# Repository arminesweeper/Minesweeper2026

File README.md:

# Assiut Robotics — Minesweeper Autonomous Rover

<p align="center">

</p>

---

## 📌 Executive Summary

The **Assiut Robotics Minesweeper Rover** is an autonomous field robotics platform engineered for humanitarian mine action and robotics competitions (*Minesweeper International / Minesweeper Egypt*). The rover combines real-time computer vision, electromagnetic/inductive sensing, optical proximity scanning, autonomous coverage planning, closed-loop motion control, and surface mine extraction mechanics into an integrated cross-layer cyber-physical system.

- **Institution:** Faculty of Engineering, Assiut University
- **Team:** Assiut Robotics Team
- **Supervisor:** Eng. Sayed Khader
- **Demonstration Video:** [YouTube — Minesweeper Robot](https://youtu.be/dL5ubC7n4h4)

---

## 📖 Master Documentation Navigation Hub

This repository contains multi-tiered engineering documentation covering software, firmware, electronics, and competition field strategy. Use the quick links below to navigate to specific subsystems:

| Document | Description | Language | Primary Location |
| :--- | :--- | :---: | :--- |
| **Competition Overview & Technical Report** | Comprehensive engineering report, real-world bug troubleshooting, competition strategy, and mathematical models | Arabic | [`Minesweeper_Competitions_Overview.md`](./Minesweeper_Competitions_Overview.md) |
| **Electronic Circuit & Hardware Report** | Full PCB schematic analysis, power distribution rails, relay drivers, connectors, and BOM | English | [`Minesweeper2026/Files/Report/report.md`](./Minesweeper2026/Files/Report/report.md) |
| **ROS 2 Workspace Manual** | Simulation, SLAM Toolbox, Navigation, Zigzag Coverage, Vision OCR, and launch guides | English | [`rover_ws/README.md`](./rover_ws/README.md) |
| **Synchronized Pinout Map** | As-fabricated Mega 2560 pin mappings, timers, interrupts, and Soft-I2C flying leads | English | [`Minesweeper2026/Arduino/MotorController/Docs/Pinout.md`](./Minesweeper2026/Arduino/MotorController/Docs/Pinout.md) |
| **Firmware Architecture** | Object-oriented modular firmware breakdown, FSM state machines, and task loop timing | English | [`Minesweeper2026/Arduino/MotorController/Docs/Architecture.md`](./Minesweeper2026/Arduino/MotorController/Docs/Architecture.md) |
| **Serial Protocol & API** | Framing, command bytes, packet checksums, and telemetry stream formats | English | [`Minesweeper2026/Arduino/MotorController/Docs/Communication.md`](./Minesweeper2026/Arduino/MotorController/Docs/Communication.md) |
| **Motion Control & PID** | Kinematics, PID math, feed-forward, deadband thresholds, and odometry formulas | English | [`Minesweeper2026/Arduino/MotorController/Docs/MotionControl.md`](./Minesweeper2026/Arduino/MotorController/Docs/MotionControl.md) |
| **Safety & Watchdog Systems** | Communication timeouts, brownout protection, limit switch safety, and E-Stop states | English | [`Minesweeper2026/Arduino/MotorController/Docs/Safety.md`](./Minesweeper2026/Arduino/MotorController/Docs/Safety.md) |
| **Wiring & Harness Manual** | Wire gauges, connector specifications, terminal assignments, and crimping guide | English | [`Minesweeper2026/Arduino/MotorController/Docs/WiringManual.md`](./Minesweeper2026/Arduino/MotorController/Docs/WiringManual.md) |
| **Operator GUI & Telemetry** | PySide6 desktop dashboard, gamepad integration, and live telemetry viewer | English | [`Minesweeper2026/GUI/README.md`](./Minesweeper2026/GUI/README.md) |
| **Legacy 2024 Archive** | Historic codebase, design iterations, and legacy project records | English | [`Minesweeper2024/README.md`](./Minesweeper2024/README.md) |

---

## 🏛️ System Architecture

The robot utilizes a **hierarchical dual-interface architecture** providing robust separation of concerns between high-level computation, real-time deterministic control, and standalone field debugging:

```mermaid
flowchart TB
    subgraph OperatorLayer["Operator & Telemetry Station"]
        OP_STATION[Operator Laptop / Gamepad]
        WEB_CLIENT[Browser Diagnostic UI / WebSockets]
    end

    subgraph HighLevelCompute["High-Level Compute — Raspberry Pi 4 (Ubuntu Linux)"]
        ROS_CORE[ROS 2 Humble Middleware]
        SLAM_NODE[SLAM Toolbox / EKF Localization]
        PLAN_NODE[Zigzag Coverage & A* Planner]
        VISION_NODE[Camera + EasyOCR Mine Classifier]
        SER_NODE[Serial Bridge Interface Node]
    end

    subgraph WirelessBypass["Field Diagnostics Bypass — ESP8266 Module"]
        ESP_CORE[ESP8266 Local Web Server]
        ESP_JOY[WASD / Touchscreen Teleop]
        ESP_TELEM[Live Battery & Sensor Telemetry]
    end

    subgraph LowLevelControl["Deterministic Embedded Controller — Arduino Mega 2560"]
        STATE_MGR[System State Machine INIT / ARMED / RUN / FAULT]
        PID_CORE[Dual Wheel PID Controller + Feed-Forward]
        MOTION_CORE[Differential Drive Inverse Kinematics]
        ODOM_CORE[Encoder Odometry Accumulator]
        SAFETY_CORE[Watchdog, Brownout & E-Stop Interlocks]
        LIFT_CORE[Surface Mine Lift & Limit Switch Sequencer]
    end

    subgraph PowerAndActuation["Power Stage & Motor Drivers"]
        BATTERY[Tianneng 12V 25Ah Graphene Battery]
        CYTRON_DRV[Cytron MDD10A Rev2.0 Dual H-Bridge]
        DRIVE_MOTORS[4x High-Torque Geared DC Drive Motors]
        LIFT_MOTOR[Tailgate Extraction Lift Motor]
        RELAY_K1[Relay K1: Electromagnet Bus MAG1-MAG5]
        RELAY_K2[Relay K2: 12V Alert Siren & Strobe]
    end

    subgraph SensorArray["Detection & Navigation Sensors"]
        ENCODERS[Quadrature Optical Encoders PPR 385]
        IMU_6DOF[MPU6050 6-DOF IMU via Soft-I2C]
        PROX_ARRAY[5x Infrared Proximity Array + OR Gate]
        COIL_MD[Pulse Induction / VLF Metal Detector Coil]
        LIMIT_SW[Travel Limit Switches Active-LOW]
        VOLT_DIV[Precision 3.3:1 Battery Voltage Divider]
    end

    OP_STATION <-->|Wi-Fi 5 GHz / TCP Socket| ROS_CORE
    WEB_CLIENT <-->|Wi-Fi 2.4 GHz AP / HTTP| ESP_CORE
    
    ROS_CORE <-->|USB Serial0 / 115200 baud| LowLevelControl
    ESP_CORE <-->|Hardware Serial2 / 115200 baud| LowLevelControl

    LowLevelControl --> CYTRON_DRV --> DRIVE_MOTORS
    LowLevelControl --> LIFT_MOTOR
    LowLevelControl --> RELAY_K1
    LowLevelControl --> RELAY_K2

    ENCODERS --> LowLevelControl
    IMU_6DOF --> LowLevelControl
    PROX_ARRAY --> LowLevelControl
    COIL_MD --> LowLevelControl
    LIMIT_SW --> LowLevelControl
    VOLT_DIV --> LowLevelControl
    BATTERY --> PowerAndActuation
```

---

## ⚙️ Technical Specifications

### Physical & Mechanical

- **Locomotion:** 4-Wheel Drive (4WD) with differential skid-steering
- **Chassis Dimensions:** Length 650 mm × Width 480 mm × Ground Clearance 85 mm
- **Wheel Specifications:** 220 mm diameter × 100 mm width rugged rubber tread
- **Track Gauge (Wheelbase):** $L = 150\text{ mm}$ (center-to-center lateral base)
- **Mine Extraction:** Motorized tailgate lift with active limit switch homing and 5× high-flux electromagnets

### Electrical & Power Distribution

- **Main Power Source:** Tianneng TNE12-25 12V 25Ah Deep-Cycle Graphene Lead-Acid Battery
- **Motor Driver:** Cytron MDD10A Rev2.0 (Dual Channel, 10A continuous / 30A peak per channel)
- **Power Rails:**
  - `12V_MAIN`: Motors, Cytron H-Bridge, and auxiliary power (Terminal `J24`, filtered with $2000\,\mu\text{F}$)
  - `12V_MG`: Dedicated electromagnet bus (Terminals `MAG1–MAG5`, filtered with $4000\,\mu\text{F}$)
  - `5V_LOGIC`: MCU logic, encoders, IMU, sensors (Terminal `J22`, filtered with $2000\,\mu\text{F}$)
  - `5V_SERVO`: Camera pan servo and auxiliary servos (Terminal `J23`/`J13`)
- **Total Bulk Decoupling Capacitance:** $> 11,000\,\mu\text{F}$ distributed to suppress inductive motor inrush

### Microcontroller & Sensors

- **Low-Level MCU:** Atmel ATmega2560 (16 MHz, 8 KB SRAM, 256 KB Flash)
- **Encoder Resolution:** 385 pulses per revolution (PPR) on output wheel shaft
- **Inertial Measurement Unit:** InvenSense MPU6050 (6-DOF Accelerometer + Gyroscope) via Soft-I2C on D31/D33
- **Surface Detection:** 5× Infrared optical proximity sensors (`APRX1–APRX5`) with hardware OR-gate aggregation
- **Subsurface Detection:** High-sensitivity inductive search coil (`J40`) for buried metallic mines

---

## 🚀 Quick Start Guide

### 1. Arduino Mega Firmware

1. Open [`Minesweeper2026/Arduino/MotorController/MotorController.ino`](./Minesweeper2026/Arduino/MotorController/MotorController.ino) in the Arduino IDE or VS Code / PlatformIO.
2. Select Board: **Arduino Mega 2560**, Processor: **ATmega2560**.
3. Verify feature flags in `Config.h`:

   ```cpp
   #define ENABLE_WATCHDOG        1
   #define ENABLE_ODOMETRY        1
   #define ENABLE_LIFT            1
   #define ENABLE_SENSORS         1
   #define USE_SOFT_I2C_FOR_IMU   1
   ```

4. Compile and flash to the Arduino Mega via USB.

### 2. Standalone ESP8266 Telemetry & Debugging Dashboard

1. Open [`Minesweeper2026/Arduino/WiFiController/`](./Minesweeper2026/Arduino/WiFiController/) in the Arduino IDE.
2. Connect an Arduino Uno with `RESET` tied to `GND` as a hardware bypass programmer (`TX` to `TX`, `RX` to `RX`).
3. Flash the code to the ESP8266.
4. Power the rover, connect your phone or laptop to the created Wi-Fi Access Point (`Minesweeper_Rover`), and browse to `http://192.168.4.1` for full manual control, battery monitoring, and telemetry.

### 3. ROS 2 Workspace (Ubuntu Linux with ROS 2 Humble)

Clone or navigate to the workspace, install system dependencies, and build:

```bash
cd rover_ws
rosdep update
rosdep install --from-paths src --ignore-src -r -y
colcon build --symlink-install
source install/setup.bash
```

#### Launching Gazebo Simulation

```bash
ros2 launch rover_bringup simulated_robot.launch.py
```

#### Launching on the Physical Robot

```bash
ros2 launch rover_bringup real_robot.launch.py
```

#### Running Joystick Teleoperation

```bash
ros2 launch rover_controller joystick_teleop.launch.py
```

---

## 📡 ROS 2 Topics & Interfaces

| Topic | Message Type | Description |
| :--- | :--- | :--- |
| `/cmd_vel` | `geometry_msgs/msg/Twist` | Target linear and angular velocity commands |
| `/odom` | `nav_msgs/msg/Odometry` | Wheel odometry fused with encoder ticks |
| `/imu/data` | `sensor_msgs/msg/Imu` | Filtered angular velocity and linear acceleration |
| `/joint_states` | `sensor_msgs/msg/JointState` | Rover wheel and lift joint positions |
| `/scan` | `sensor_msgs/msg/LaserScan` | 2D LiDAR range scan for obstacle avoidance |
| `/map` | `nav_msgs/msg/OccupancyGrid` | Live SLAM occupancy grid map |
| `/coverage_path` | `nav_msgs/msg/Path` | Zigzag lawnmower path generated by planner |
| `/mine_detected` | `rover_msgs/msg/MineAlert` | Detected mine payload (type: surface/buried, position: x, y) |

---

## 🛠️ Field Troubleshooting Matrix

Summary of the 12 verified physical hardware and firmware issues resolved during field testing (detailed root cause analysis available in [`Minesweeper_Competitions_Overview.md`](./Minesweeper_Competitions_Overview.md)):

| # | Symptom | Root Cause | Verified Resolution |
| :-: | :--- | :--- | :--- |
| **1** | Severe lagging & high loop latency | RTOS-like multi-tasking overload on ATmega2560 | Enabled compile-time feature flags in `Config.h` to disable unused modules |
| **2** | Motors deadlocked upon boot (`FAULT`) | Watchdog started counting before first command | Modified `Safety.cpp` to start timeout only after first valid command |
| **3** | Gripper stalled or moving violently | Floating limit pins + PWM set to 220 (86% power) | Activated `INPUT_PULLUP` and clamped `LIFT_PWM_SPEED` to 90 (35% power) |
| **4** | Limit switch dashboard inverted | Pins D51 and D53 swapped vs physical wiring | Swapped definitions in `Config.h` (`D51` = Bottom, `D53` = Top) |
| **5** | MPU6050 I²C bus deadlock | Shield copper wired ENC1 to D20/D21 (Hardware I²C) | Implemented Soft-I2C on D31/D33 with external flying leads |
| **6** | Alert siren continuously blaring | Driver circuit is Active-LOW via NPN transistor | Changed `#define SIREN_ACTIVE_HIGH 0` in `Config.h` |
| **7** | Inverted proximity readings | Hardware OR-gate output floating without threshold | Adjusted `PROXIMITY_THRESHOLD` to 500 and added calibration offsets |
| **8** | ESP8266 flashing timeout error | Arduino Mega serial passthrough dropped high-speed bytes | Used Arduino Uno hardware bypass (`RESET` to `GND`) for flashing |
| **9** | Rover stopping every 2s in web UI | Browser `keydown` only fired once; watchdog timed out | Implemented 100ms periodic retransmission loop in web frontend |
| **10** | ESP8266 unable to boot with divider | 10kΩ divider resistor placed adjacent to `EN`/`RST` pin | Isolated divider directly to ADC `A0` pin away from boot-strap lines |
| **11** | Electromagnet overheating | 100% duty cycle 12V applied continuously | Implemented 8s auto-off safety cutoff timer in firmware |
| **12** | ROS 2 motion jerky and unresponsive | Blocking serial read calls on main thread | Rewrote ROS serial bridge with non-blocking async threads at 20 Hz |

---

## 📋 Pre-Flight Commissioning Checklist

Before deploying the rover onto the competition field or test arena:

```markdown
1. Battery Health: Verify open-circuit voltage >= 12.6V (Do not operate below 11.8V).
2. Mechanical Fasteners: Inspect wheel hubs, motor brackets, and lift linkages for play.
3. Bench Motor Direction Check: Elevate chassis; command forward motion; verify both wheels spin forward.
4. Encoder Calibration: Rotate each wheel 1 full revolution by hand; verify ~385 counts accumulated.
5. Watchdog Fail-safe: Disconnect serial cable while motors run; verify complete motor shutdown within 1.5s.
6. Limit Switches: Manually depress top/bottom switches; confirm instantaneous lift motor deactivation.
7. Sensor Simulation: Pass metallic and surface mine samples; verify blue status LEDs illuminate and siren triggers.
8. Wire Harness Dress: Inspect Soft-I2C flying leads; ensure separation from high-current motor cables.
```

---

## 👥 Contributors & Team

- **Assiut Robotics Team — Faculty of Engineering, Assiut University**
- **Academic Supervisor:** Eng. Sayed Khader
- **Firmware, Controls & Hardware Review:** Control & Embedded Systems Engineering Sub-team

---

## 📄 License

This repository is released under the MIT License for educational, humanitarian demining research, and non-commercial competition purposes.

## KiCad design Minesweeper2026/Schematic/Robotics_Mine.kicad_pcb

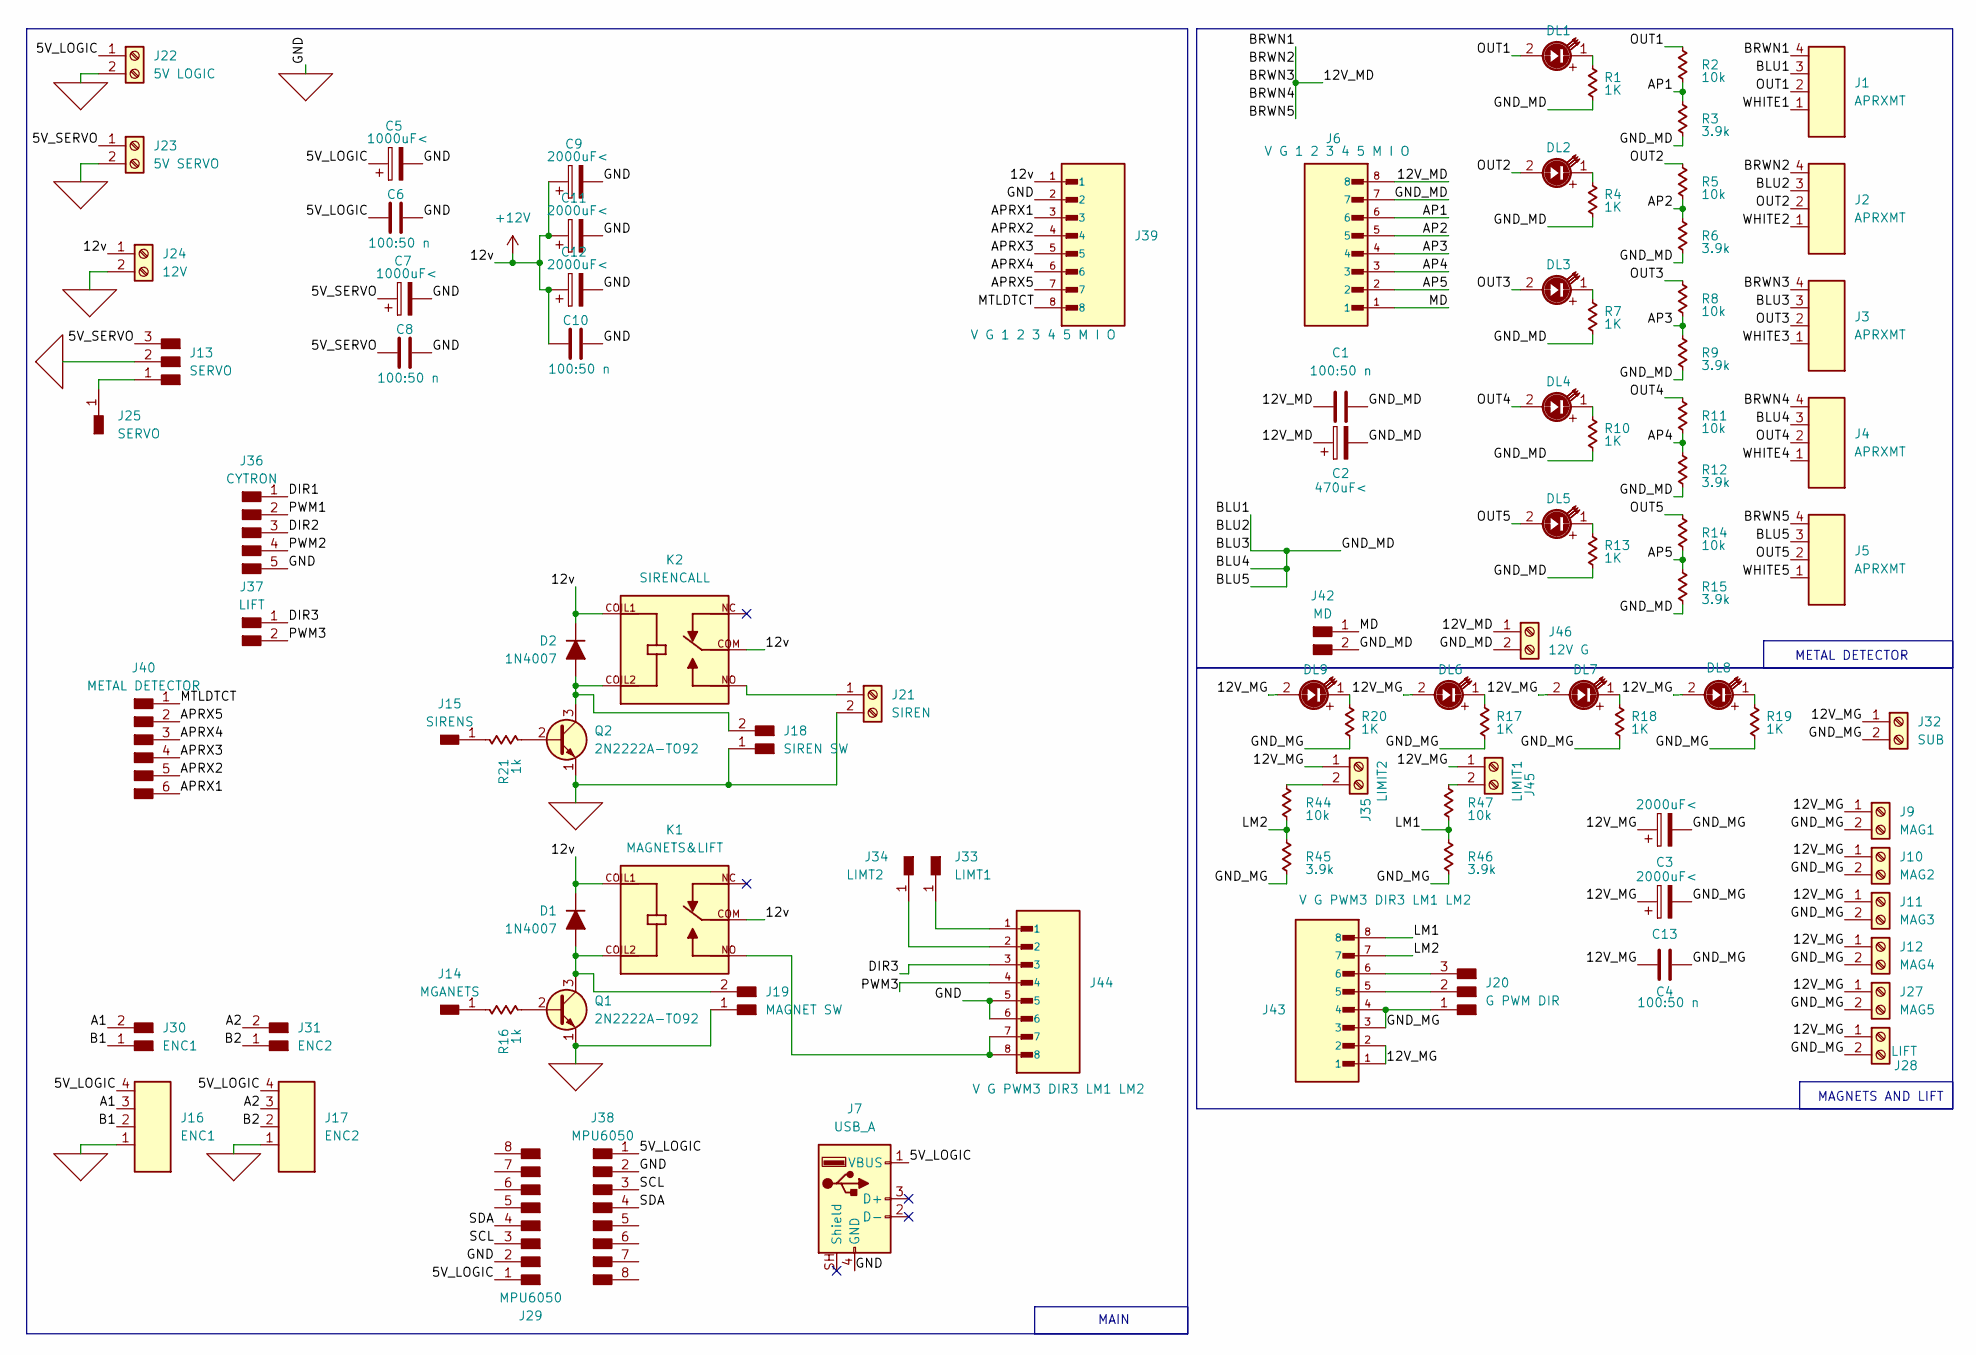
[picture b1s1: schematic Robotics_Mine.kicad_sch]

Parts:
C1, C4, C6, C8, C10: 100:50 n; C_Disc_D3.0mm_W1.6mm_P2.50mm
C2: 470uF<; CP_Radial_D10.0mm_P5.00mm
C3, C9, C11, C12, C13: 2000uF<; CP_Radial_D10.0mm_P5.00mm
C5, C7: 1000uF<; CP_Radial_D10.0mm_P5.00mm
D1, D2: 1N4007; D_DO-41_SOD81_P7.62mm_Horizontal
DL1, DL2, DL3, DL4, DL5, DL6, DL7, DL8, DL9: LED_D3.0mm
J1, J2, J3, J4, J5: APRXMT; JST_S4B-XH-A
J6, J39: V G 1 2 3 4 5 M I O; JST_S8B-XH-A-1; PARTREV N/A
J7: USB_A; USB_A_Connfly_DS1095
J9: MAG1; TerminalBlock_OnShore_1x02_P5.00mm_Horizontal
J10: MAG2; TerminalBlock_OnShore_1x02_P5.00mm_Horizontal
J11: MAG3; TerminalBlock_OnShore_1x02_P5.00mm_Horizontal
J12: MAG4; TerminalBlock_OnShore_1x02_P5.00mm_Horizontal
J13: SERVO; PinHeader_01x03_P2.54mm_Vertical_THT_D1.4mm
J14: MGANETS; PinHeader_01x01_P2.54mm_Vertical_THT_D1.4mm
J15: SIRENS; PinHeader_01x01_P2.54mm_Vertical_THT_D1.4mm
J16: ENC1; JST_XH_B4B-XH-A_1x04_P2.50mm_Vertical
J17: ENC2; JST_XH_B4B-XH-A_1x04_P2.50mm_Vertical
J18: SIREN SW; PinHeader_01x02_P2.54mm_Vertical_THT_D1.4mm
J19: MAGNET SW; PinHeader_01x02_P2.54mm_Vertical_THT_D1.4mm
J20: G PWM DIR; PinHeader_01x03_P2.54mm_Vertical_THT_D1.4mm
J21: SIREN; TerminalBlock_OnShore_1x02_P5.00mm_Horizontal
J22: 5V LOGIC; TerminalBlock_OnShore_1x02_P5.00mm_Horizontal
J23: 5V SERVO; TerminalBlock_OnShore_1x02_P5.00mm_Horizontal
J24: 12V; TerminalBlock_OnShore_1x02_P5.00mm_Horizontal
J25: SERVO; PinHeader_01x01_P2.54mm_Vertical_THT_D1.4mm
J27: MAG5; TerminalBlock_OnShore_1x02_P5.00mm_Horizontal
J28: LIFT; TerminalBlock_OnShore_1x02_P5.00mm_Horizontal
J29, J38: MPU6050; PinHeader_01x08_P2.54mm_Vertical_THT_D1.4mm
J30: ENC1; PinHeader_01x02_P2.54mm_Vertical_THT_D1.4mm
J31: ENC2; PinHeader_01x02_P2.54mm_Vertical_THT_D1.4mm
J32: SUB; TerminalBlock_OnShore_1x02_P5.00mm_Horizontal
J33: LIMT1; PinHeader_01x01_P2.54mm_Vertical_THT_D1.4mm
J34: LIMT2; PinHeader_01x01_P2.54mm_Vertical_THT_D1.4mm
J35: LIMIT2; TerminalBlock_OnShore_1x02_P5.00mm_Horizontal
J36: CYTRON; PinHeader_01x05_P2.54mm_Vertical_THT_D1mm
J37: LIFT; PinHeader_01x02_P2.54mm_Vertical_THT_D1.4mm
J40: METAL DETECTOR; PinHeader_01x06_P2.54mm_Vertical_THT_D1.4mm
J42: MD; PinHeader_01x02_P2.54mm_Vertical_THT_D1.4mm
J43, J44: V G PWM3 DIR3 LM1 LM2; JST_S8B-XH-A-1; PARTREV N/A
J45: LIMIT1; TerminalBlock_OnShore_1x02_P5.00mm_Horizontal
J46: 12V G; TerminalBlock_OnShore_1x02_P5.00mm_Horizontal
K1: MAGNETS&LIFT; RELAY_SRD-12VDC-SL-C; PARTREV 1.0
K2: SIRENCALL; RELAY_SRD-12VDC-SL-C; PARTREV 1.0
Q1, Q2: 2N2222A-TO92; TO-92_Inline_Wide_EBC
R1, R4, R7, R10, R13, R17, R18, R19, R20: 1K; R_Axial_DIN0207_L6.3mm_D2.5mm_P7.62mm_Horizontal
R2, R5, R8, R11, R14: 10k; R_Axial_DIN0207_L6.3mm_D2.5mm_P7.62mm_Horizontal
R3, R6, R9, R12, R15: 3.9k; R_Axial_DIN0207_L6.3mm_D2.5mm_P7.62mm_Horizontal
R16, R21: 1k; R_Axial_DIN0207_L6.3mm_D2.5mm_P7.62mm_Horizontal
R44, R47: 10k; R_Axial_DIN0204_L3.6mm_D1.6mm_P7.62mm_Horizontal
R45, R46: 3.9k; R_Axial_DIN0204_L3.6mm_D1.6mm_P7.62mm_Horizontal

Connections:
4: J13.1, J25.1 (Pin_1_1)
12: J38.8
13: J38.7
+12V: C9.1, C10.1, C11.1, C12.1, D1.1 (K), D2.1 (K), J24.1, J39.1, K1.COIL1, K1.COM, K2.COIL1, K2.COM
/5V_LOGIC: C5.1, C6.1, J7.1 (VBUS), J16.4, J17.4, J22.1, J29.1, J38.1; also elsewhere on the board
/5V_SERVO: C7.1, C8.1, J13.3, J23.1
/12V_MD: C1.1, C2.1, J1.4, J2.4, J3.4, J4.4, J5.4, J6.8, J46.1
/12V_MG: C3.1, C4.1, C13.1, DL6.2, DL7.2, DL8.2, DL9.2, J9.1, J10.1, J11.1, J12.1, J27.1, J28.1, J32.1, J35.1, J43.1, J43.2, J45.1
/A1: J16.3, J30.2
/A2: J17.3, J31.2
/AP1: J6.6, R2.2 (-), R3.1 (+)
/AP2: J6.5, R5.2 (-), R6.1 (+)
/AP3: J6.4, R8.2 (-), R9.1 (+)
/AP4: J6.3, R11.2 (-), R12.1 (+)
/AP5: J6.2, R14.2 (-), R15.1 (+)
/APRX1: J39.3, J40.6
/APRX2: J39.4, J40.5
/APRX3: J39.5, J40.4
/APRX4: J39.6, J40.3
/APRX5: J39.7, J40.2
/B1: J16.2, J30.1
/B2: J17.2, J31.1
/BLU1: C1.2, C2.2, J1.3, J2.3, J3.3, J4.3, J5.3, J6.7, J42.2, J46.2, R1.2 (-), R3.2 (-), R4.2 (-), R6.2 (-), R7.2 (-), R9.2 (-), R10.2 (-), R12.2 (-), R13.2 (-), R15.2 (-)
/DIR1: J36.1
/DIR2: J36.3
/DIR3: J37.1, J44.3
/GND_MG: C3.2, C4.2, C13.2, J9.2, J10.2, J11.2, J12.2, J20.1, J27.2, J28.2, J32.2, J43.3, J43.4, R17.2 (-), R18.2 (-), R19.2 (-), R20.2 (-), R45.2 (-), R46.2 (-)
/LM1: J43.8, R46.1 (+), R47.2 (-)
/LM2: J43.7, R44.2 (-), R45.1 (+)
/MD: J6.1, J42.1
/MTLDTCT: J39.8, J40.1
/OUT1: DL1.2, J1.2, R2.1 (+)
/OUT2: DL2.2, J2.2, R5.1 (+)
/OUT3: DL3.2, J3.2, R8.1 (+)
/OUT4: DL4.2, J4.2, R11.1 (+)
/OUT5: DL5.2, J5.2, R14.1 (+)
/PWM1: J36.2
/PWM2: J36.4
/PWM3: J37.2, J44.4
/SCL: J29.3, J38.3
/SDA: J29.4, J38.4
/WHITE1: J1.1
/WHITE2: J2.1
/WHITE3: J3.1
/WHITE4: J4.1
/WHITE5: J5.1
unnamed: D1.2 (A), J19.2, K1.COIL2, Q1.3 (C)
unnamed: D2.2 (A), J18.2, K2.COIL2, Q2.3 (C)
unnamed: J14.1 (Pin_1_1), R16.1 (+)
unnamed: J15.1 (Pin_1_1), R21.1 (+)
unnamed: J20.2, J43.5
unnamed: J20.3, J43.6
unnamed: J21.1, K2.NO
unnamed: J33.1 (Pin_1_1), J44.1
unnamed: J34.1 (Pin_1_1), J44.2
unnamed: J35.2, R44.1 (+)
unnamed: J44.7, J44.8, K1.NO
unnamed: J45.2, R47.1 (+)
unnamed: Q1.2 (B), R16.2 (-)
unnamed: Q2.2 (B), R21.2 (-)
unnamed: DL1.1, R1.1 (+)
unnamed: DL2.1, R4.1 (+)
unnamed: DL3.1, R7.1 (+)
unnamed: DL4.1, R10.1 (+)
unnamed: DL5.1, R13.1 (+)
unnamed: DL6.1, R17.1 (+)
unnamed: DL7.1, R18.1 (+)
unnamed: DL8.1, R19.1 (+)
unnamed: DL9.1, R20.1 (+)
P,GND: C5.2, C6.2, C7.2, C8.2, C9.2, C10.2, C11.2, C12.2, J7.4 (GND), J13.2, J16.1, J17.1, J18.1, J19.1, J21.2, J22.2, J23.2, J24.2, J29.2, J36.5, J38.2, J39.2, J44.5, J44.6, Q1.1 (E), Q2.1 (E); also elsewhere on the board

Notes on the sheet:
MAIN
MAGNETS AND LIFT
METAL DETECTOR

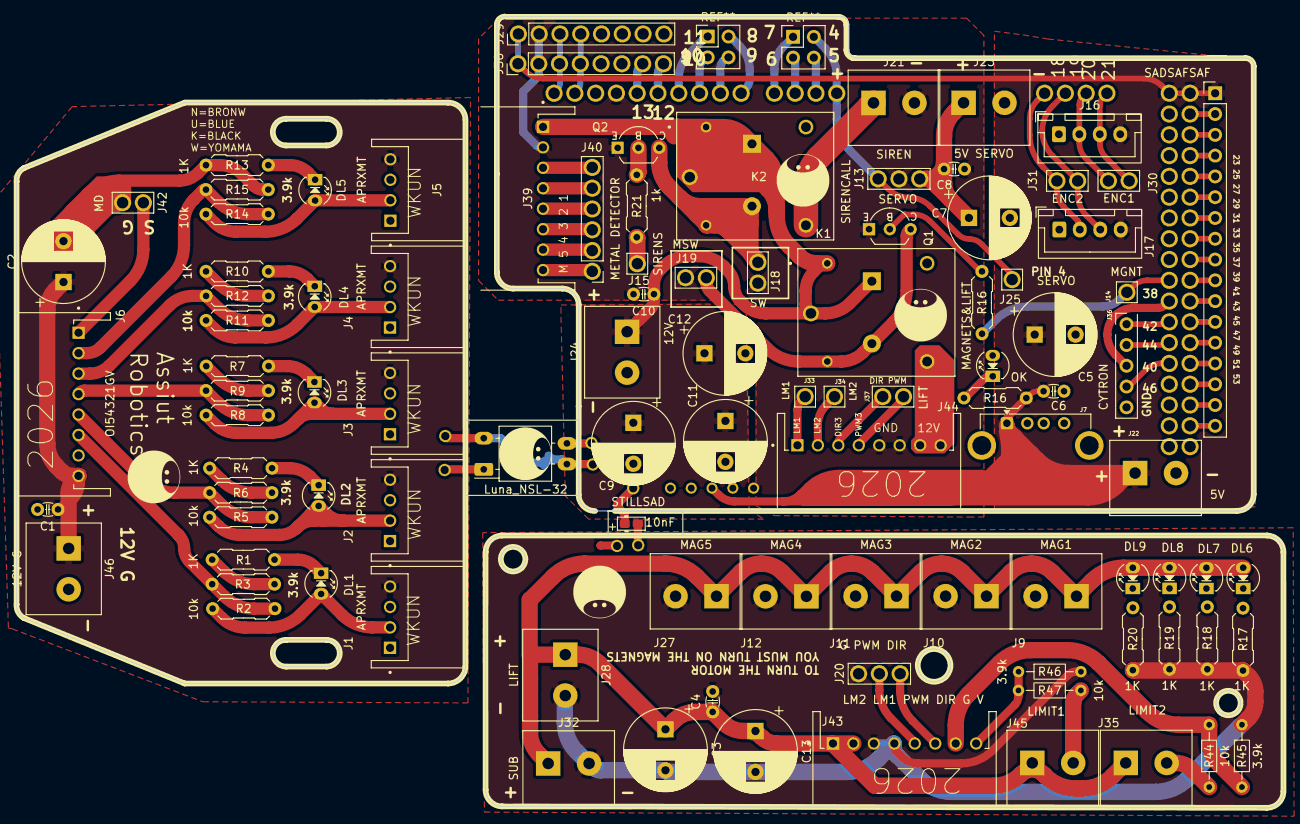
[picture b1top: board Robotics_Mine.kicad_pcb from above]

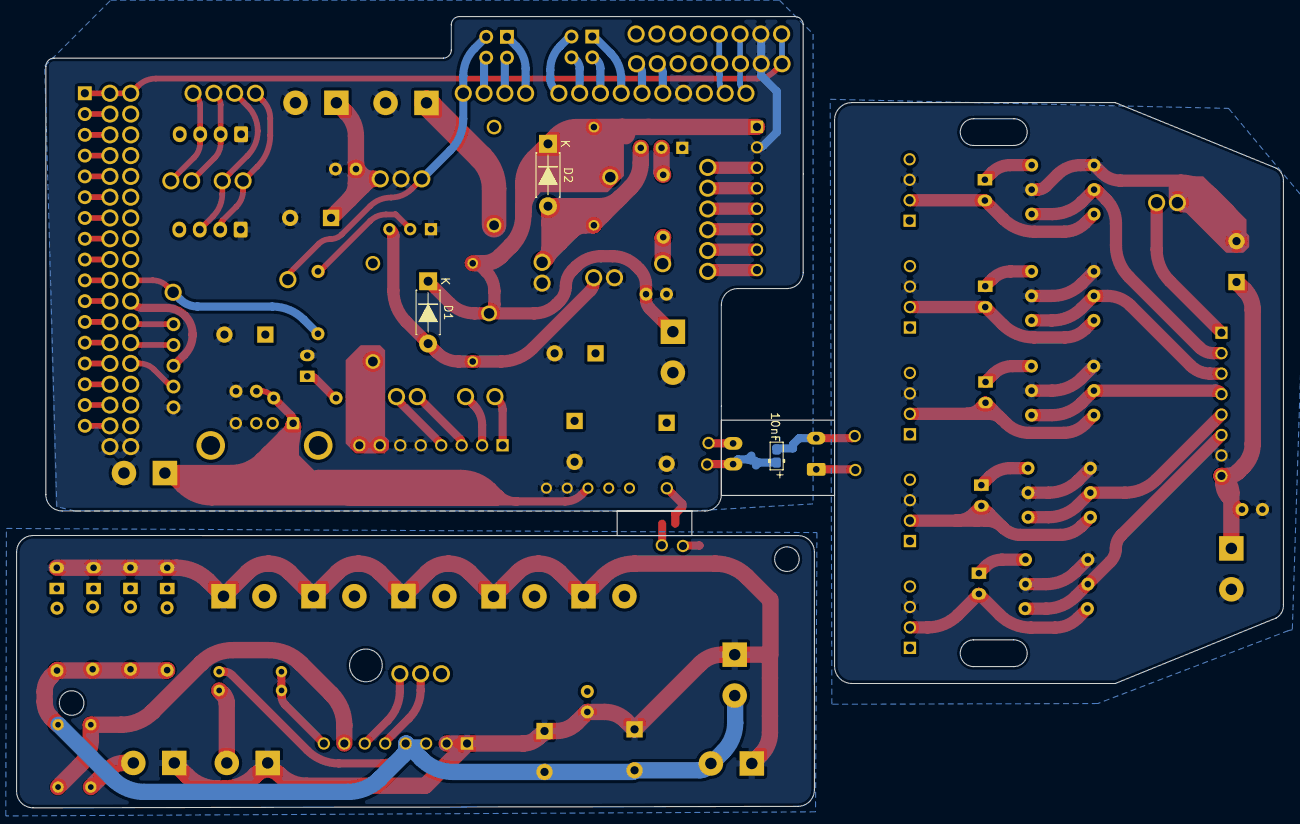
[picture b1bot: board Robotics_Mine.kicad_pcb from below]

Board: 2 copper layers, 154.8 x 96.7 mm, 99 parts (2 on the bottom side), 60 nets.

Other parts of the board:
OK: LED_D3.0mm
R16#2: 1k; R_Axial_DIN0207_L6.3mm_D2.5mm_P7.62mm_Horizontal
SADSAFSAF: PinHeader_1x17_P2.54mm_Vertical

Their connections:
/5V_LOGIC: R16#2.1 (+), SADSAFSAF.1; also elsewhere on the board
P,GND: OK.2; also elsewhere on the board
red: OK.1, R16#2.2 (-)

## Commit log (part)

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2026-06-12 organize Minesweeper2024
